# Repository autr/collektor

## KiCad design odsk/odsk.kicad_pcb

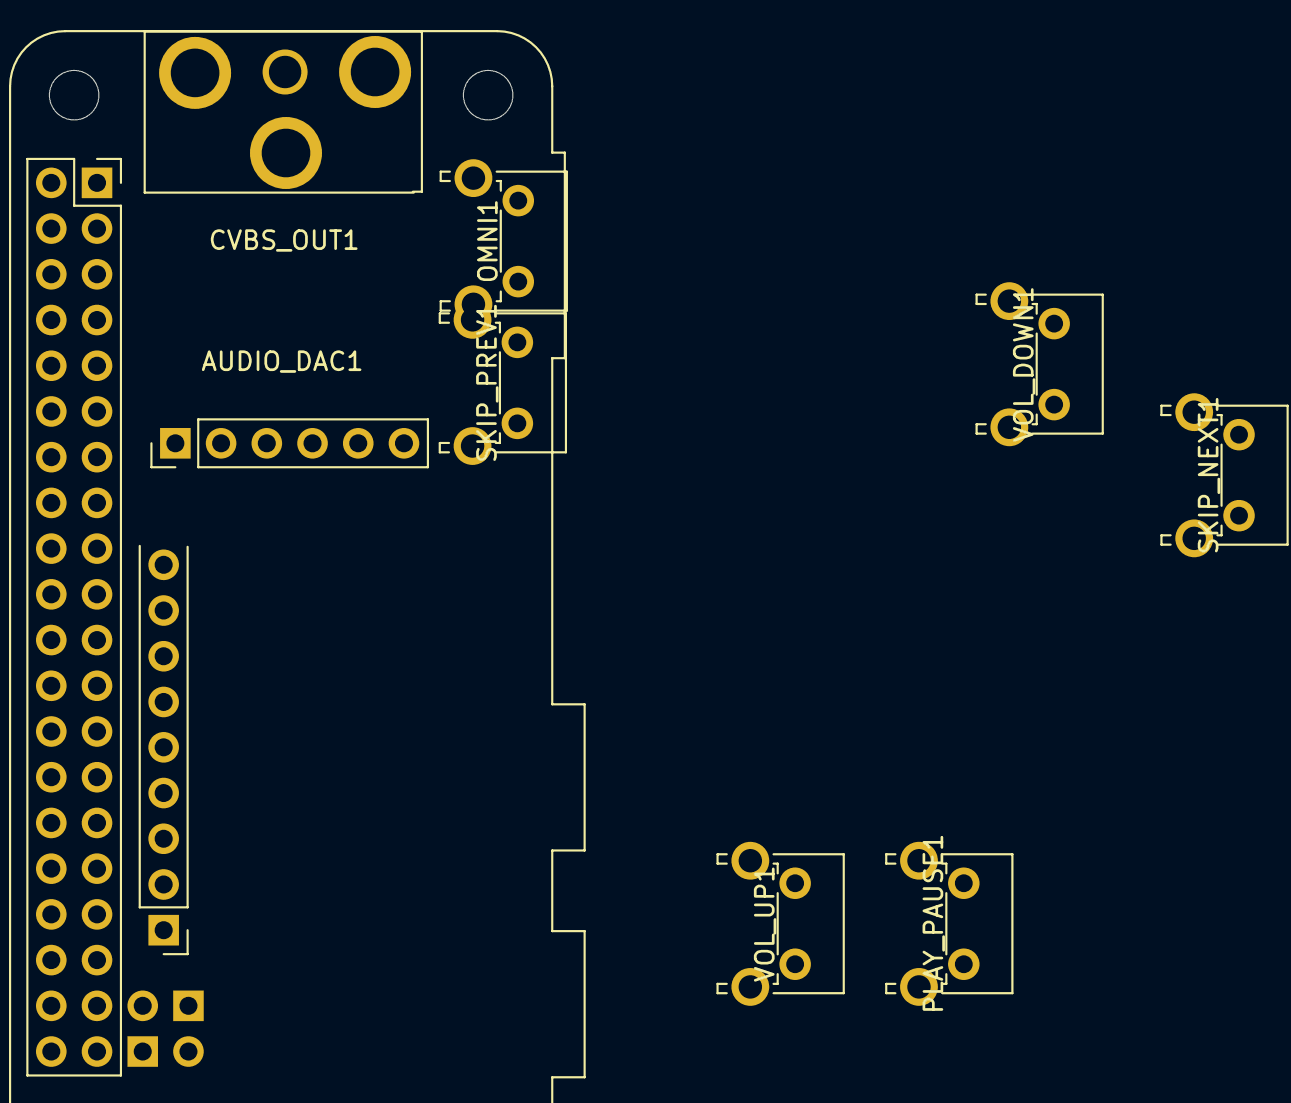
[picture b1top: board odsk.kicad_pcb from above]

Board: 2 copper layers, 9 parts (0 on the bottom side), 12 nets, no tracks yet.

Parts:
AUDIO_DAC1: PCM5102; rpiPCM5102
CVBS_OUT1: Conn_Coaxial; rca_angle_RCJ01
OMNI1: SW_SPST; SW_Tactile_SPST_Angled_PTS645Vx39-2LFS
PI_ZERO1: Raspberry_Pi_Zero
PLAY_PAUSE1: SW_SPST; SW_Tactile_SPST_Angled_PTS645Vx39-2LFS
SKIP_NEXT1: SW_SPST; SW_Tactile_SPST_Angled_PTS645Vx39-2LFS
SKIP_PREV1: SW_SPST; SW_Tactile_SPST_Angled_PTS645Vx39-2LFS
VOL_DOWN1: SW_SPST; SW_Tactile_SPST_Angled_PTS645Vx39-2LFS
VOL_UP1: SW_SPST; SW_Tactile_SPST_Angled_PTS645Vx39-2LFS

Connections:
GND: AUDIO_DAC1.10, AUDIO_DAC1.14, CVBS_OUT1.2, OMNI1.2, PI_ZERO1.6, PI_ZERO1.9, PI_ZERO1.14, PI_ZERO1.20, PI_ZERO1.25, PI_ZERO1.30, PI_ZERO1.34, PI_ZERO1.39, PLAY_PAUSE1.2, SKIP_NEXT1.2, SKIP_PREV1.2, VOL_DOWN1.2, VOL_UP1.2
unnamed: AUDIO_DAC1.11, PI_ZERO1.12
unnamed: AUDIO_DAC1.12, PI_ZERO1.40
unnamed: AUDIO_DAC1.13, PI_ZERO1.35
unnamed: AUDIO_DAC1.15, PI_ZERO1.1, PI_ZERO1.17
unnamed: CVBS_OUT1.1, PI_ZERO1.41
unnamed: OMNI1.1, PI_ZERO1.24
unnamed: PI_ZERO1.19, PLAY_PAUSE1.1
unnamed: PI_ZERO1.21, VOL_DOWN1.1
unnamed: PI_ZERO1.23, SKIP_NEXT1.1
unnamed: PI_ZERO1.26, SKIP_PREV1.1
unnamed: PI_ZERO1.32, VOL_UP1.1

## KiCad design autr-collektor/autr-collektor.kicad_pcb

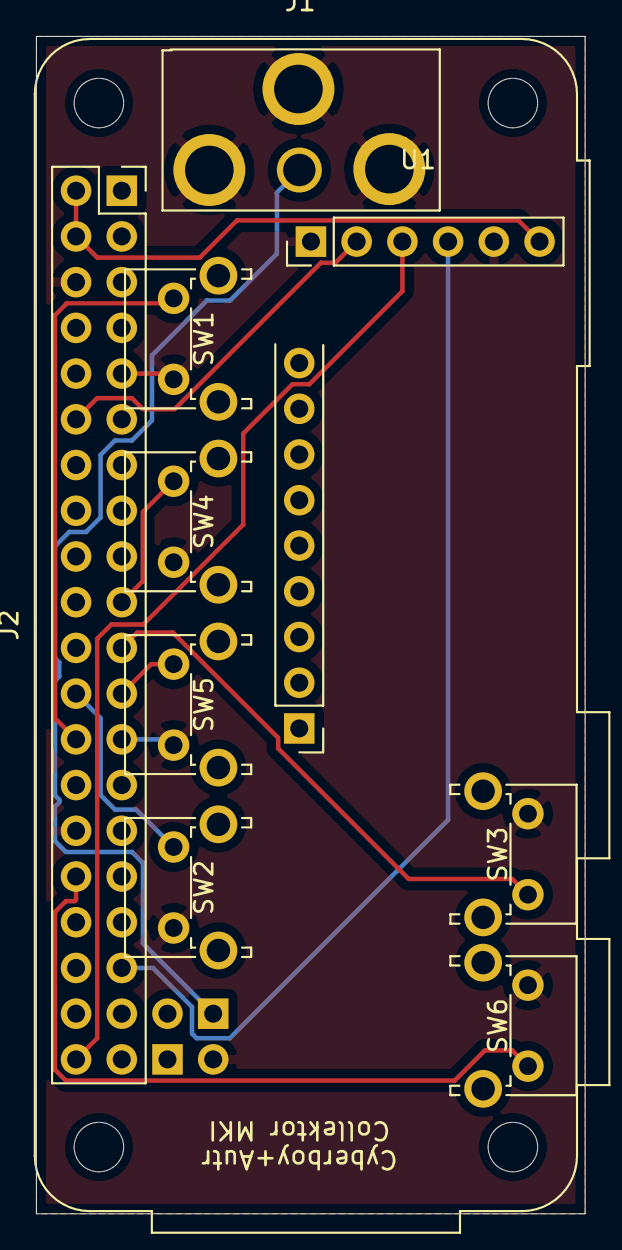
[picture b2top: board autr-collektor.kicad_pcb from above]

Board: 2 copper layers, 30.5 x 65.4 mm, 9 parts (0 on the bottom side), 12 nets.

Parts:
J1: Conn_Coaxial; rca_angle_RCJ01
J2: Raspberry_Pi_Zero
SW1, SW2, SW3, SW4, SW5, SW6: SW_SPST; SW_Tactile_SPST_Angled_PTS645Vx39-2LFS
U1: PCM5102; rpiPCM5102

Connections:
GND: J1.2, J2.6, J2.9, J2.14, J2.20, J2.25, J2.30, J2.34, J2.39, J2.42, SW1.1, SW2.1, SW3.1, SW4.1, SW5.1, SW6.1, U1.10, U1.14
unnamed: J1.1, J2.41
unnamed: J2.2, J2.4, U1.15
unnamed: J2.12, U1.11
unnamed: J2.19, SW4.2
unnamed: J2.21, SW3.2
unnamed: J2.23, SW5.2
unnamed: J2.24, SW2.2
unnamed: J2.26, SW1.2
unnamed: J2.32, SW6.2
unnamed: J2.35, U1.13
unnamed: J2.40, U1.12

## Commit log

2020-10-02 init
2020-10-02 rm old script
2020-10-02 kicad files v1
2021-08-07 odsk
